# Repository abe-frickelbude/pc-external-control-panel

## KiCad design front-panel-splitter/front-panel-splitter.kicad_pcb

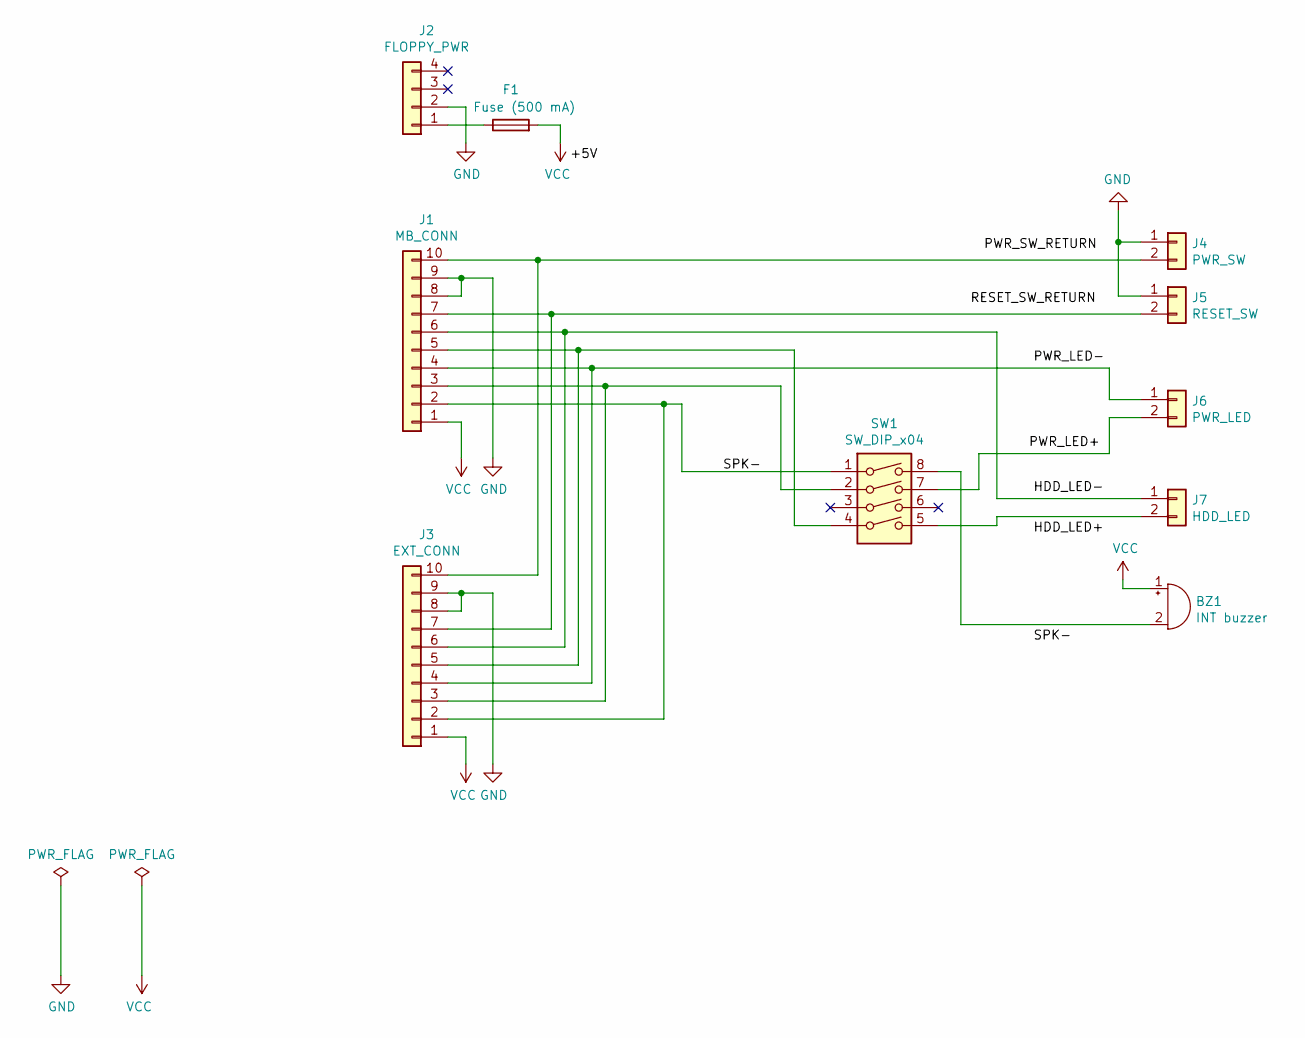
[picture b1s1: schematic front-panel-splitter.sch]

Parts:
BZ1: INT buzzer; Buzzer_12x9.5RM7.6
F1: Fuse (500 mA); Fuseholder_Fuse_TR5_Littlefuse-No560_No460
J1: MB_CONN; Pin_Header_Straight_1x10_Pitch2.54mm
J2: FLOPPY_PWR; Molex_KK-6410-04_04x2.54mm_Straight
J3: EXT_CONN; Pin_Header_Straight_1x10_Pitch2.54mm
J4: PWR_SW; Pin_Header_Straight_1x02_Pitch2.54mm
J5: RESET_SW; Pin_Header_Straight_1x02_Pitch2.54mm
J6: PWR_LED; Pin_Header_Straight_1x02_Pitch2.54mm
J7: HDD_LED; Pin_Header_Straight_1x02_Pitch2.54mm
SW1: SW_DIP_x04; SW_DIP_x4_W7.62mm_Slide

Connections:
/SPK-: J1.2, J3.2, SW1.1
GND: J1.8, J1.9, J2.2, J3.8, J3.9, J4.1, J5.1
unnamed: BZ1.2 (+), SW1.8
unnamed: F1.1, J2.1
unnamed: J1.3, J3.3, SW1.2
unnamed: J1.4, J3.4, J6.1
unnamed: J1.5, J3.5, SW1.4
unnamed: J1.6, J3.6, J7.1
unnamed: J1.7, J3.7, J5.2
unnamed: J1.10, J3.10, J4.2
unnamed: J6.2, SW1.7
unnamed: J7.2, SW1.5
VCC: BZ1.1 (-), F1.2, J1.1, J3.1

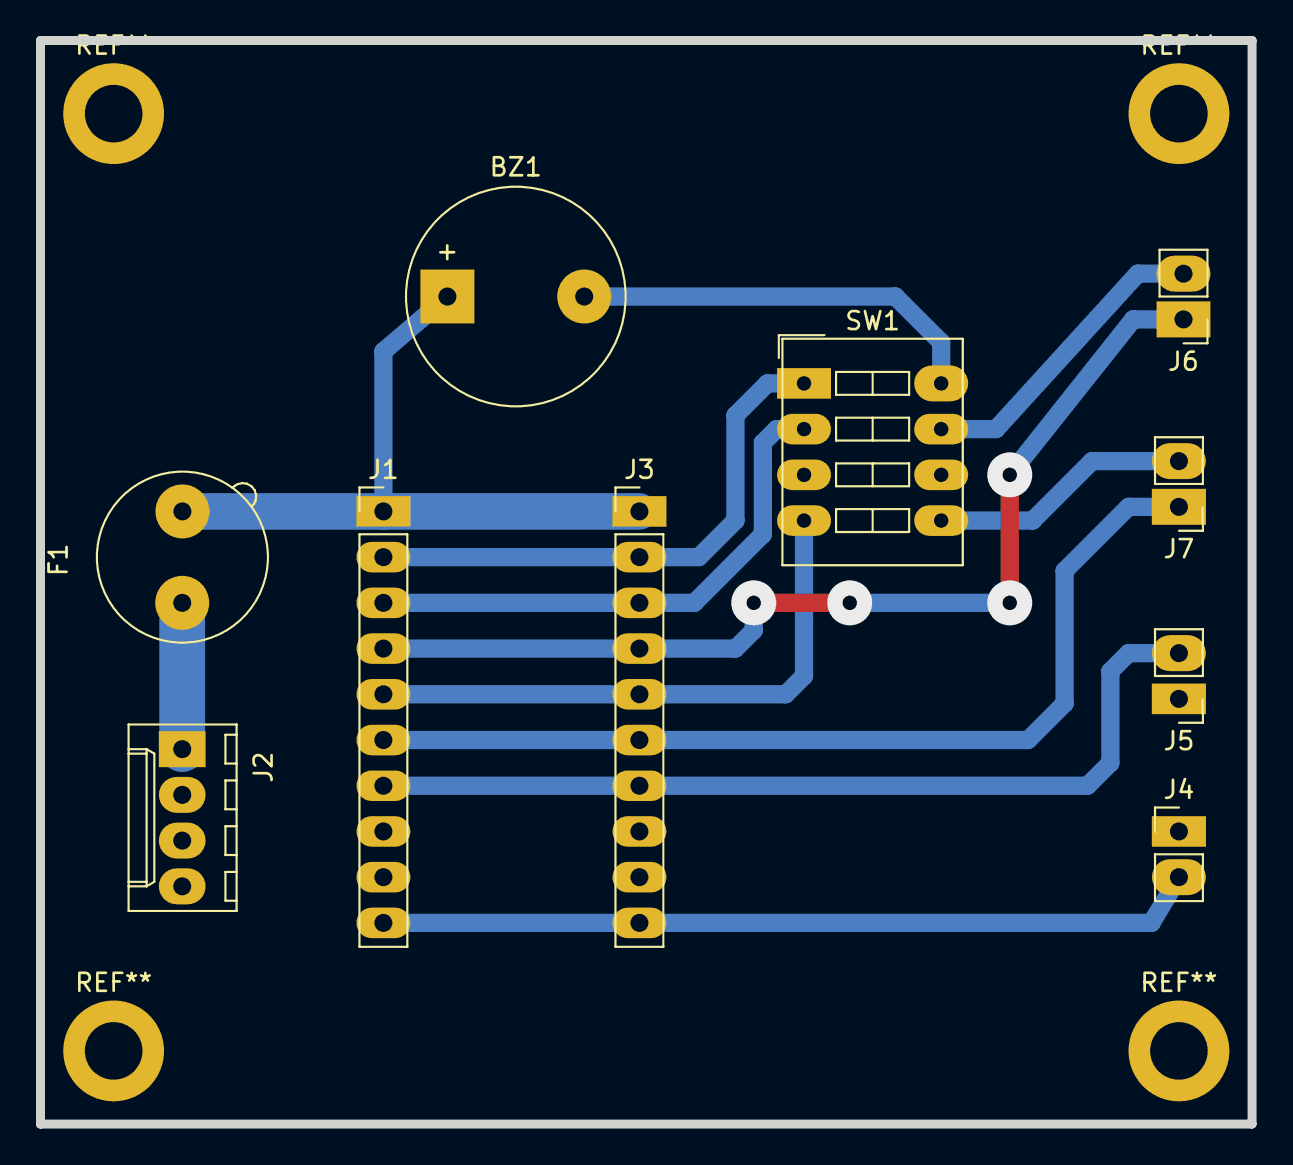
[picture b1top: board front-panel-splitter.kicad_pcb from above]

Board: 2 copper layers, 67.3 x 60.2 mm, 10 parts (0 on the bottom side), 13 nets.

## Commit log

2020-11-27 front panel signal splitter schematic / board
